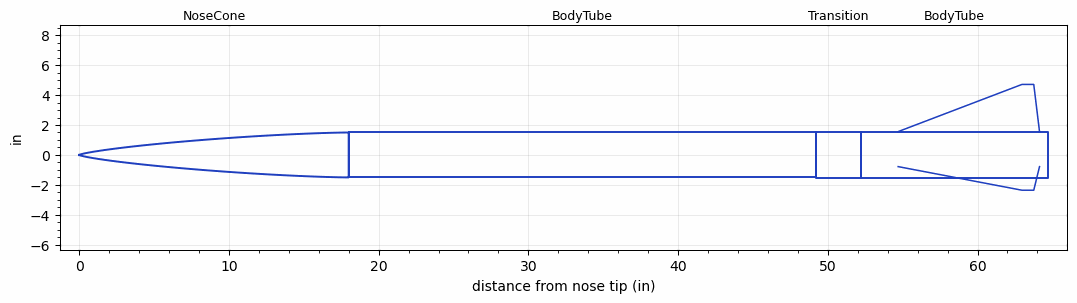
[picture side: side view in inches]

<RASAeroDocument>
 <FileVersion>2</FileVersion>
 <RocketDesign>
  <NoseCone>
   <Length>18</Length>
   <Diameter>3</Diameter>
   <Shape>Von Karman Ogive</Shape>
   <Location>0</Location>
  </NoseCone>
  <BodyTube>
   <Length>31.2</Length>
   <Diameter>3</Diameter>
   <Location>18</Location>
  </BodyTube>
  <Transition>
   <Length>3</Length>
   <Diameter>3.12</Diameter>
   <Location>49.2</Location>
   <RearDiameter>3.12</RearDiameter>
  </Transition>
  <BodyTube>
   <Length>12.5</Length>
   <Diameter>3.12</Diameter>
   <Location>52.2</Location>
   <Fin>
    <Count>3</Count>
    <Chord>9.44</Chord>
    <Span>3.15</Span>
    <SweepDistance>8.2677</SweepDistance>
    <TipChord>0.7874</TipChord>
    <Thickness>0.188</Thickness>
    <Location>10</Location>
    <AirfoilSection>Double Wedge</AirfoilSection>
    <FX1>2</FX1>
   </Fin>
  </BodyTube>
  <Surface>Camouflage Paint</Surface>
  <ModifiedBarrowman>False</ModifiedBarrowman>
  <Turbulence>False</Turbulence>
  <UseBooster1>False</UseBooster1>
  <UseBooster2>False</UseBooster2>
 </RocketDesign>
 <LaunchSite>
  <Altitude>0</Altitude>
  <Pressure>0</Pressure>
  <RodAngle>0</RodAngle>
  <RodLength>4</RodLength>
  <Temperature>74</Temperature>
  <WindSpeed>0</WindSpeed>
 </LaunchSite>
 <Recovery>
  <Altitude1>1000</Altitude1>
  <Altitude2>1000</Altitude2>
  <DeviceType1>None</DeviceType1>
  <DeviceType2>None</DeviceType2>
  <Event1>False</Event1>
  <Event2>False</Event2>
  <Size1>1</Size1>
  <Size2>1</Size2>
  <EventType1>None</EventType1>
  <EventType2>None</EventType2>
  <CD1>1.33</CD1>
  <CD2>1.33</CD2>
 </Recovery>
 <SimulationList>
  <Simulation>
   <SustainerEngine>M3400LB  (LR)</SustainerEngine>
   <SustainerLaunchWt>21.26</SustainerLaunchWt>
   <SustainerCG>41.33</SustainerCG>
   <SustainerIgnitionDelay>0</SustainerIgnitionDelay>
   <Booster1SeparationDelay>0</Booster1SeparationDelay>
   <Booster1IgnitionDelay>0</Booster1IgnitionDelay>
   <IncludeBooster1>False</IncludeBooster1>
   <Booster2Delay>0</Booster2Delay>
   <IncludeBooster2>False</IncludeBooster2>
   <TimetoApogee>44.51854</TimetoApogee>
   <MaxAltitude>45343.62</MaxAltitude>
   <MaxVelocity>3605.042</MaxVelocity>
  </Simulation>
 </SimulationList>
</RASAeroDocument>
